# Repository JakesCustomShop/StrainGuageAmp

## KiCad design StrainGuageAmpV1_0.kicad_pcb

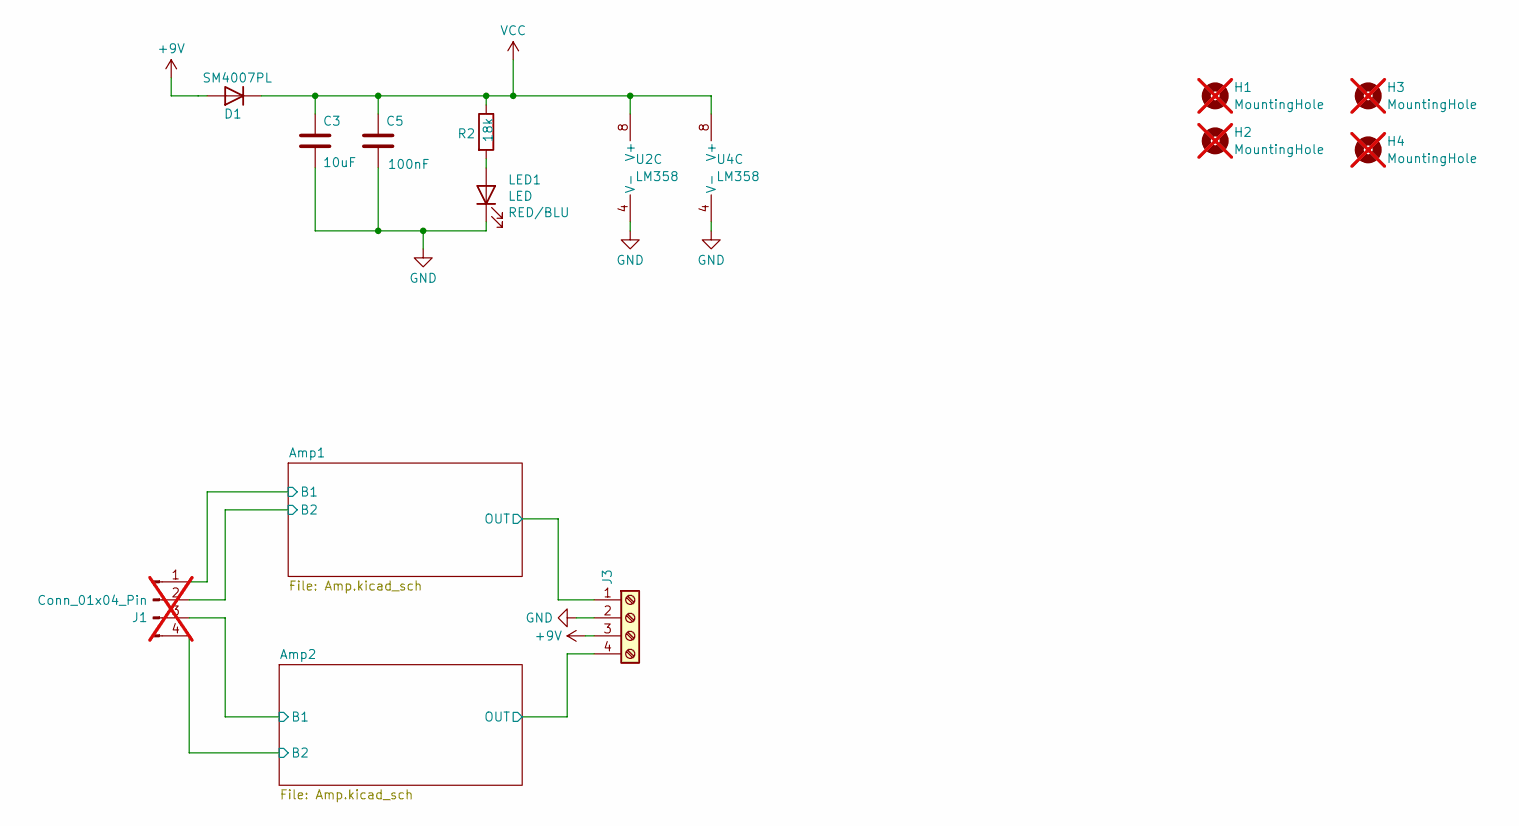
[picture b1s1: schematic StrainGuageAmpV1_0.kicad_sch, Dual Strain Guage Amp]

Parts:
C3: 10uF; C_0805_2012Metric; LCSC C15850
C5: 100nF; C_0805_2012Metric; LCSC C49678
D1: SM4007PL; D_SOD-123F; LCSC C64898
H1, H2, H3, H4: MountingHole; MountingHole_2.2mm_M2; not fitted
J1: Conn_01x04_Pin; PinHeader_1x04_P2.54mm_Vertical; not fitted
J3: Screw_Terminal_01x04; TerminalBlock_Phoenix_MKDS-1,5-4-5.08_1x04_P5.08mm_Horizont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; LCSC C2827883
LED1: LED; LED_0805_2012Metric; LCSC C2297
R2: 18k; R_0805_2012Metric; LCSC C17506
U2, U4: LM358; SOIC-8_3.9x4.9mm_P1.27mm; LCSC C5423

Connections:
+9V: D1.2 (A), J3.3
/Amp1/B1: J1.1; also elsewhere on the board
/Amp1/OUT: J3.1; also elsewhere on the board
/Amp1/VFF: J1.2; also elsewhere on the board
/Amp2/B1: J1.3; also elsewhere on the board
/Amp2/OUT: J3.4; also elsewhere on the board
/Amp2/VFF: J1.4; also elsewhere on the board
GND: C3.2, C5.2, J3.2, LED1.1 (K), U2.4 (V-), U4.4 (V-); also elsewhere on the board
unnamed: LED1.2 (A), R2.2
VCC: C3.1, C5.1, D1.1 (K), R2.1, U2.8 (V+), U4.8 (V+); also elsewhere on the board

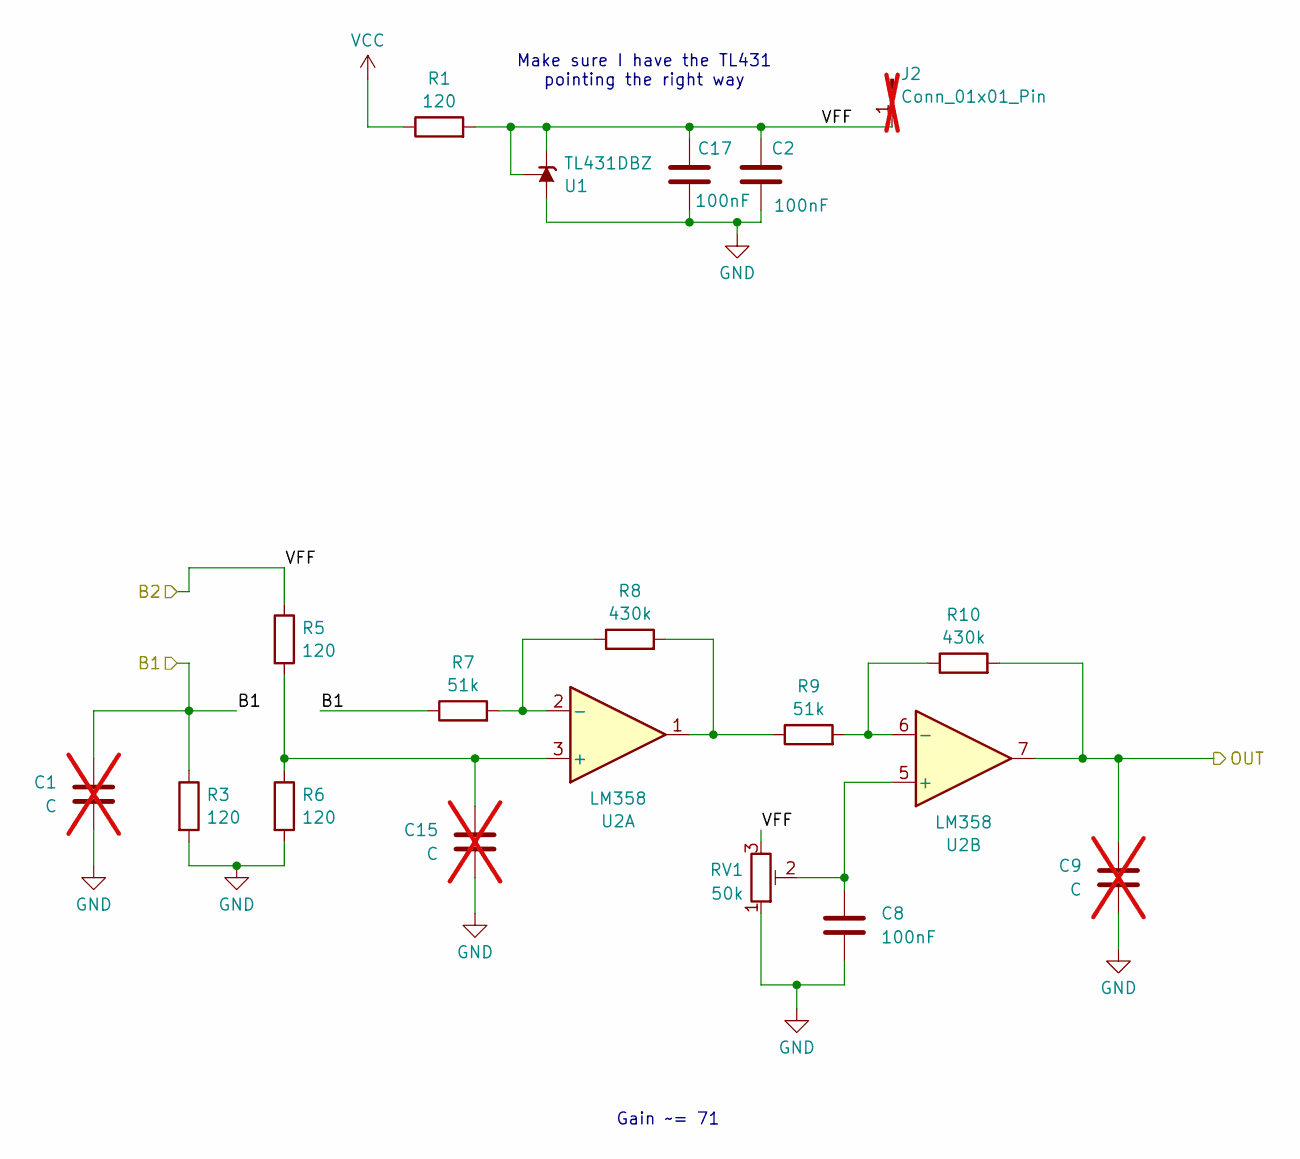
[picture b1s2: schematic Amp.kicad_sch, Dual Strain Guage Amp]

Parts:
C1, C9, C15: C; C_0805_2012Metric; not fitted
C2, C8, C17: 100nF; C_0805_2012Metric; LCSC C49678
J2: Conn_01x01_Pin; PinHeader_1x01_P2.54mm_Vertical; not fitted
R1, R3, R5, R6: 120; R_0805_2012Metric; LCSC C17437
R7, R9: 51k; R_0805_2012Metric; LCSC C17737
R8, R10: 430k; R_0805_2012Metric; LCSC C2930199
RV1: 50k; Potentiometer_Bourns_3296W_Vertical; LCSC C118911
U1: TL431DBZ; SOT-23; LCSC C23892
U2: LM358; SOIC-8_3.9x4.9mm_P1.27mm; LCSC C5423

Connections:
/Amp1/B1: C1.1, R3.1, R7.1; also elsewhere on the board
/Amp1/OUT: C9.1, R10.2, U2.7; also elsewhere on the board
/Amp1/VFF: C2.1, C17.1, J2.1, R1.2, R5.1, RV1.3, U1.1 (K), U1.2 (REF); also elsewhere on the board
GND: C1.2, C2.2, C8.2, C9.2, C15.2, C17.2, R3.2, R6.2, RV1.1, U1.3 (A); also elsewhere on the board
unnamed: R8.2, R9.1, U2.1
unnamed: C15.1, R5.2, R6.1, U2.3 (+)
unnamed: R7.2, R8.1, U2.2 (-)
unnamed: C8.1, RV1.2, U2.5 (+)
unnamed: R9.2, R10.1, U2.6 (-)
VCC: R1.1; also elsewhere on the board

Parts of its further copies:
C7, C13, C18: 100nF; C_0805_2012Metric; LCSC C49678
C10, C14, C16: C; C_0805_2012Metric; not fitted
J4: Conn_01x01_Pin; PinHeader_1x01_P2.54mm_Vertical; not fitted
R11, R12, R13, R14: 120; R_0805_2012Metric; LCSC C17437
R16, R18: 51k; R_0805_2012Metric; LCSC C17737
R17, R19: 430k; R_0805_2012Metric; LCSC C2930199
RV2: 50k; Potentiometer_Bourns_3296W_Vertical; LCSC C118911
U3: TL431DBZ; SOT-23; LCSC C23892

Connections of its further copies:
/Amp2/B1: C10.1, R12.1, R16.1; also elsewhere on the board
/Amp2/OUT: C14.1, R19.2; also elsewhere on the board
/Amp2/VFF: C7.1, C18.1, J4.1, R11.2, R13.1, RV2.3, U3.1 (K), U3.2 (REF); also elsewhere on the board
GND: C7.2, C10.2, C13.2, C14.2, C16.2, C18.2, R12.2, R14.2, RV2.1, U3.3 (A); also elsewhere on the board
unnamed 10: R17.2, R18.1; also elsewhere on the board
unnamed 15: C16.1, R13.2, R14.1; also elsewhere on the board
unnamed 16: R16.2, R17.1; also elsewhere on the board
unnamed 17: C13.1, RV2.2; also elsewhere on the board
unnamed 18: R18.2, R19.1; also elsewhere on the board
VCC: R11.1; also elsewhere on the board

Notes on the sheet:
Gain ~= 71
Make sure I have the TL431 pointing the right way

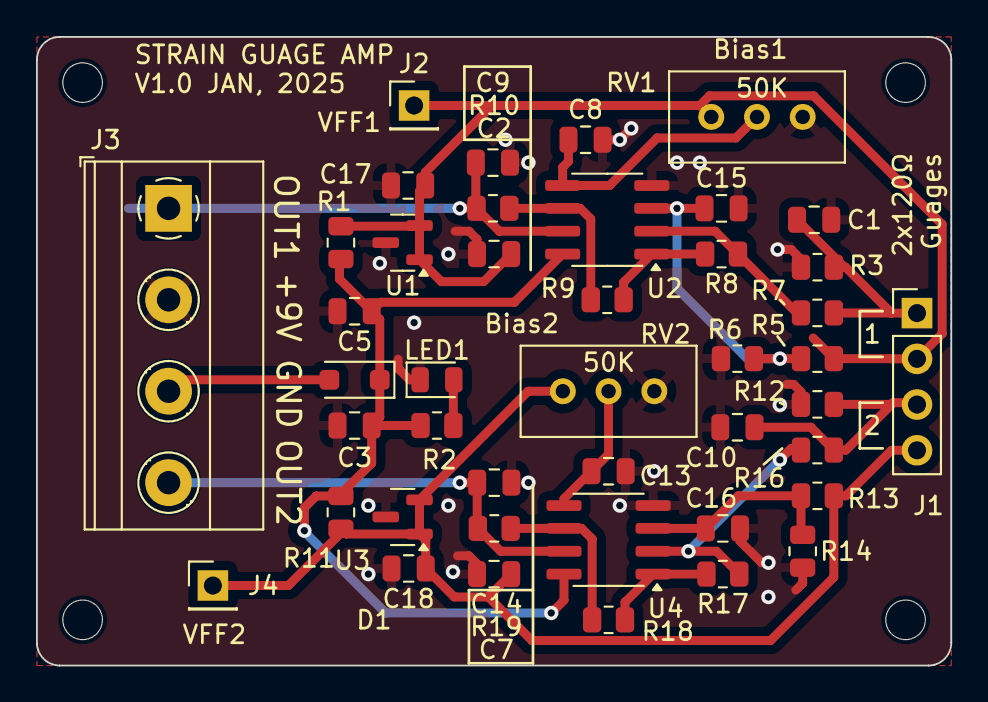
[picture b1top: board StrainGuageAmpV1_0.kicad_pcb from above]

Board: 2 copper layers, 50.8 x 34.9 mm, 47 parts (0 on the bottom side), 20 nets.

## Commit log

2025-01-28 Version V1.0 Ordered
